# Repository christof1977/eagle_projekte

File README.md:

# eagle_projekte
Eagle Projekte

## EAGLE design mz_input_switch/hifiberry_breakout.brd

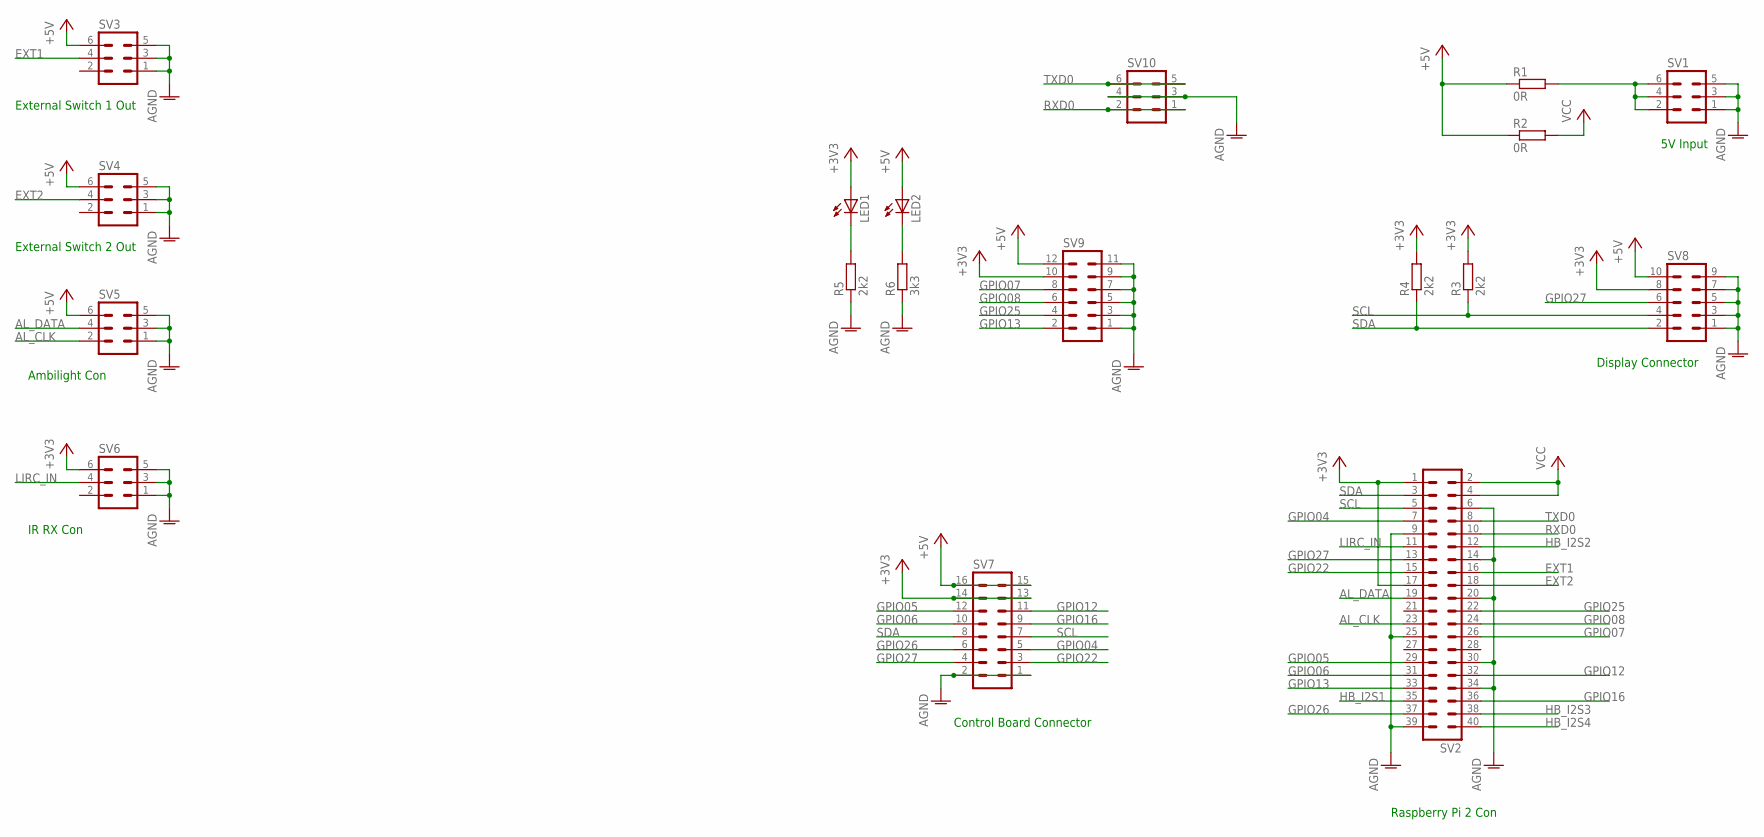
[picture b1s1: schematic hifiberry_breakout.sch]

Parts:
LED1, LED2: LEDCHIPLED_0603; CHIPLED_0603
R1, R2: 0R; R1206
R3, R4, R5: 2k2; R0603
R6: 3k3; R0603
SV1, SV3, SV4, SV5, SV6, SV10: MA03-2
SV2: MA20-2
SV7: MA08-2
SV8: MA05-2
SV9: MA06-2

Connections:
+3V3: LED1.A, R3.2, R4.2, SV2.1, SV2.17, SV6.6, SV7.13, SV7.14, SV8.8, SV9.10
+5V: LED2.A, R1.1, R2.1, SV3.6, SV4.6, SV5.6, SV7.15, SV7.16, SV8.10, SV9.12
AGND: R5.1, R6.1, SV1.1, SV1.3, SV1.5, SV2.6, SV2.9, SV2.14, SV2.20, SV2.25, SV2.30, SV2.34, SV2.39, SV3.1, SV3.3, SV3.5, SV4.1, SV4.3, SV4.5, SV5.1, SV5.3, SV5.5, SV6.1, SV6.3, SV6.5, SV7.1, SV7.2, SV8.1, SV8.3, SV8.5, SV8.7, SV8.9, SV9.1, SV9.3, SV9.5, SV9.7, SV9.9, SV9.11, SV10.3, SV10.4
AL_CLK: SV2.23, SV5.2
AL_DATA: SV2.19, SV5.4
EXT1: SV2.16, SV3.4
EXT2: SV2.18, SV4.4
GPIO04: SV2.7, SV7.5
GPIO05: SV2.29, SV7.12
GPIO06: SV2.31, SV7.10
GPIO07: SV2.26, SV9.8
GPIO08: SV2.24, SV9.6
GPIO12: SV2.32, SV7.11
GPIO13: SV2.33, SV9.2
GPIO16: SV2.36, SV7.9
GPIO22: SV2.15, SV7.3
GPIO25: SV2.22, SV9.4
GPIO26: SV2.37, SV7.6
GPIO27: SV2.13, SV7.4, SV8.6
HB_I2S1: SV2.35
HB_I2S2: SV2.12
HB_I2S3: SV2.38
HB_I2S4: SV2.40
LIRC_IN: SV2.11, SV6.4
unnamed: LED2.C, R6.2
unnamed: R1.2, SV1.2, SV1.4, SV1.6
unnamed: LED1.C, R5.2
RXD0: SV2.10, SV10.1, SV10.2
SCL: R3.1, SV2.5, SV7.7, SV8.4
SDA: R4.1, SV2.3, SV7.8, SV8.2
TXD0: SV2.8, SV10.5, SV10.6
VCC: R2.2, SV2.2, SV2.4

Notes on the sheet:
5V Input
External Switch 1 Out
External Switch 2 Out
Ambilight Con
IR RX Con
Raspberry Pi 2 Con
Control Board Connector
Display Connector

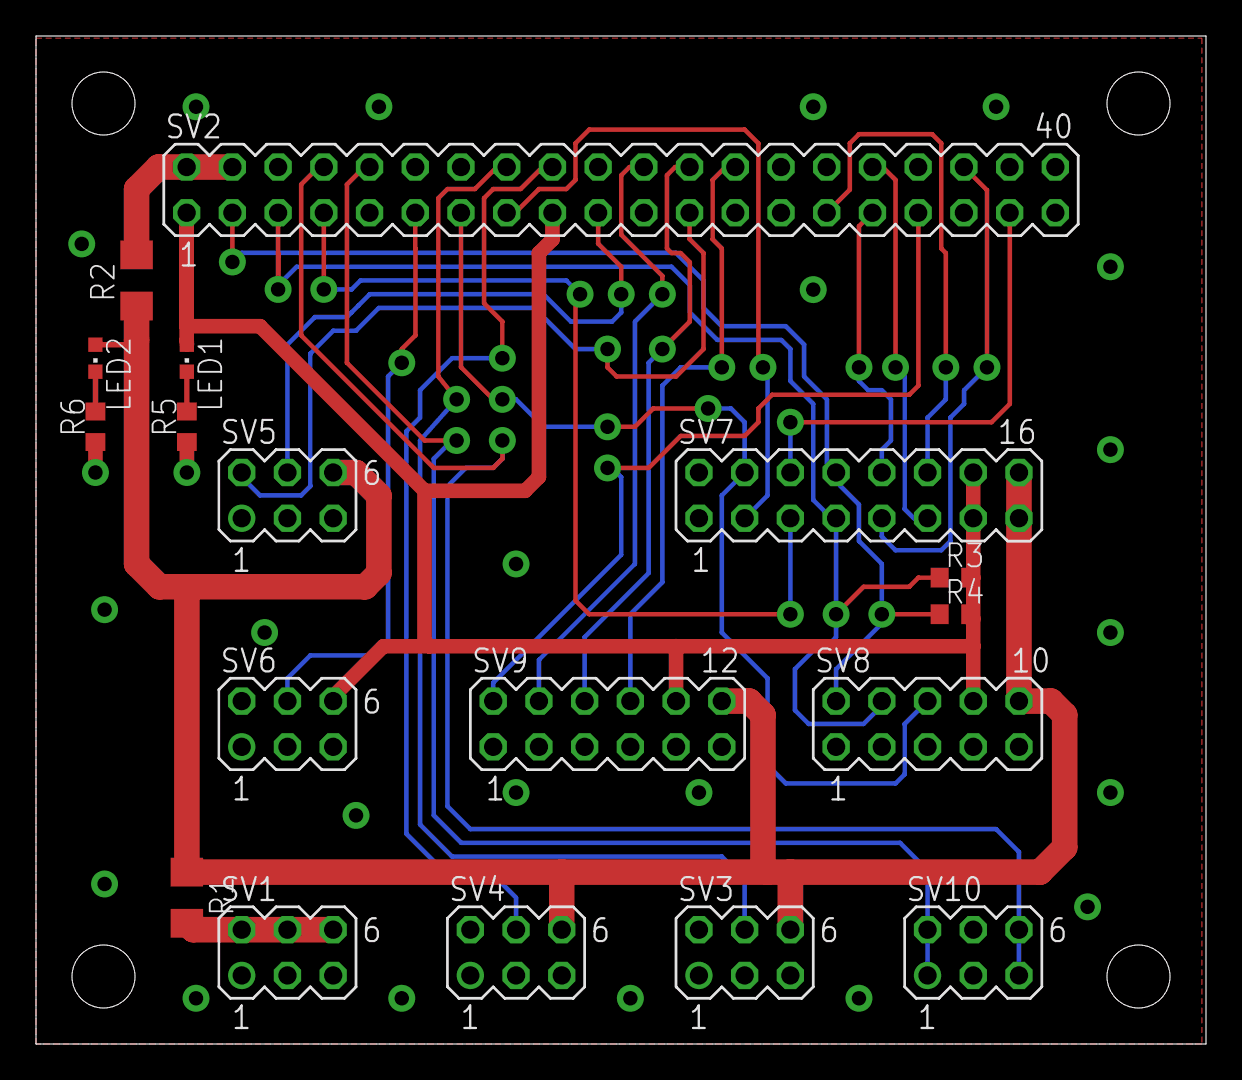
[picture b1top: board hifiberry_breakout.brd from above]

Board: 2 copper layers, 65.0 x 56.0 mm, 18 parts (0 on the bottom side), 28 nets.

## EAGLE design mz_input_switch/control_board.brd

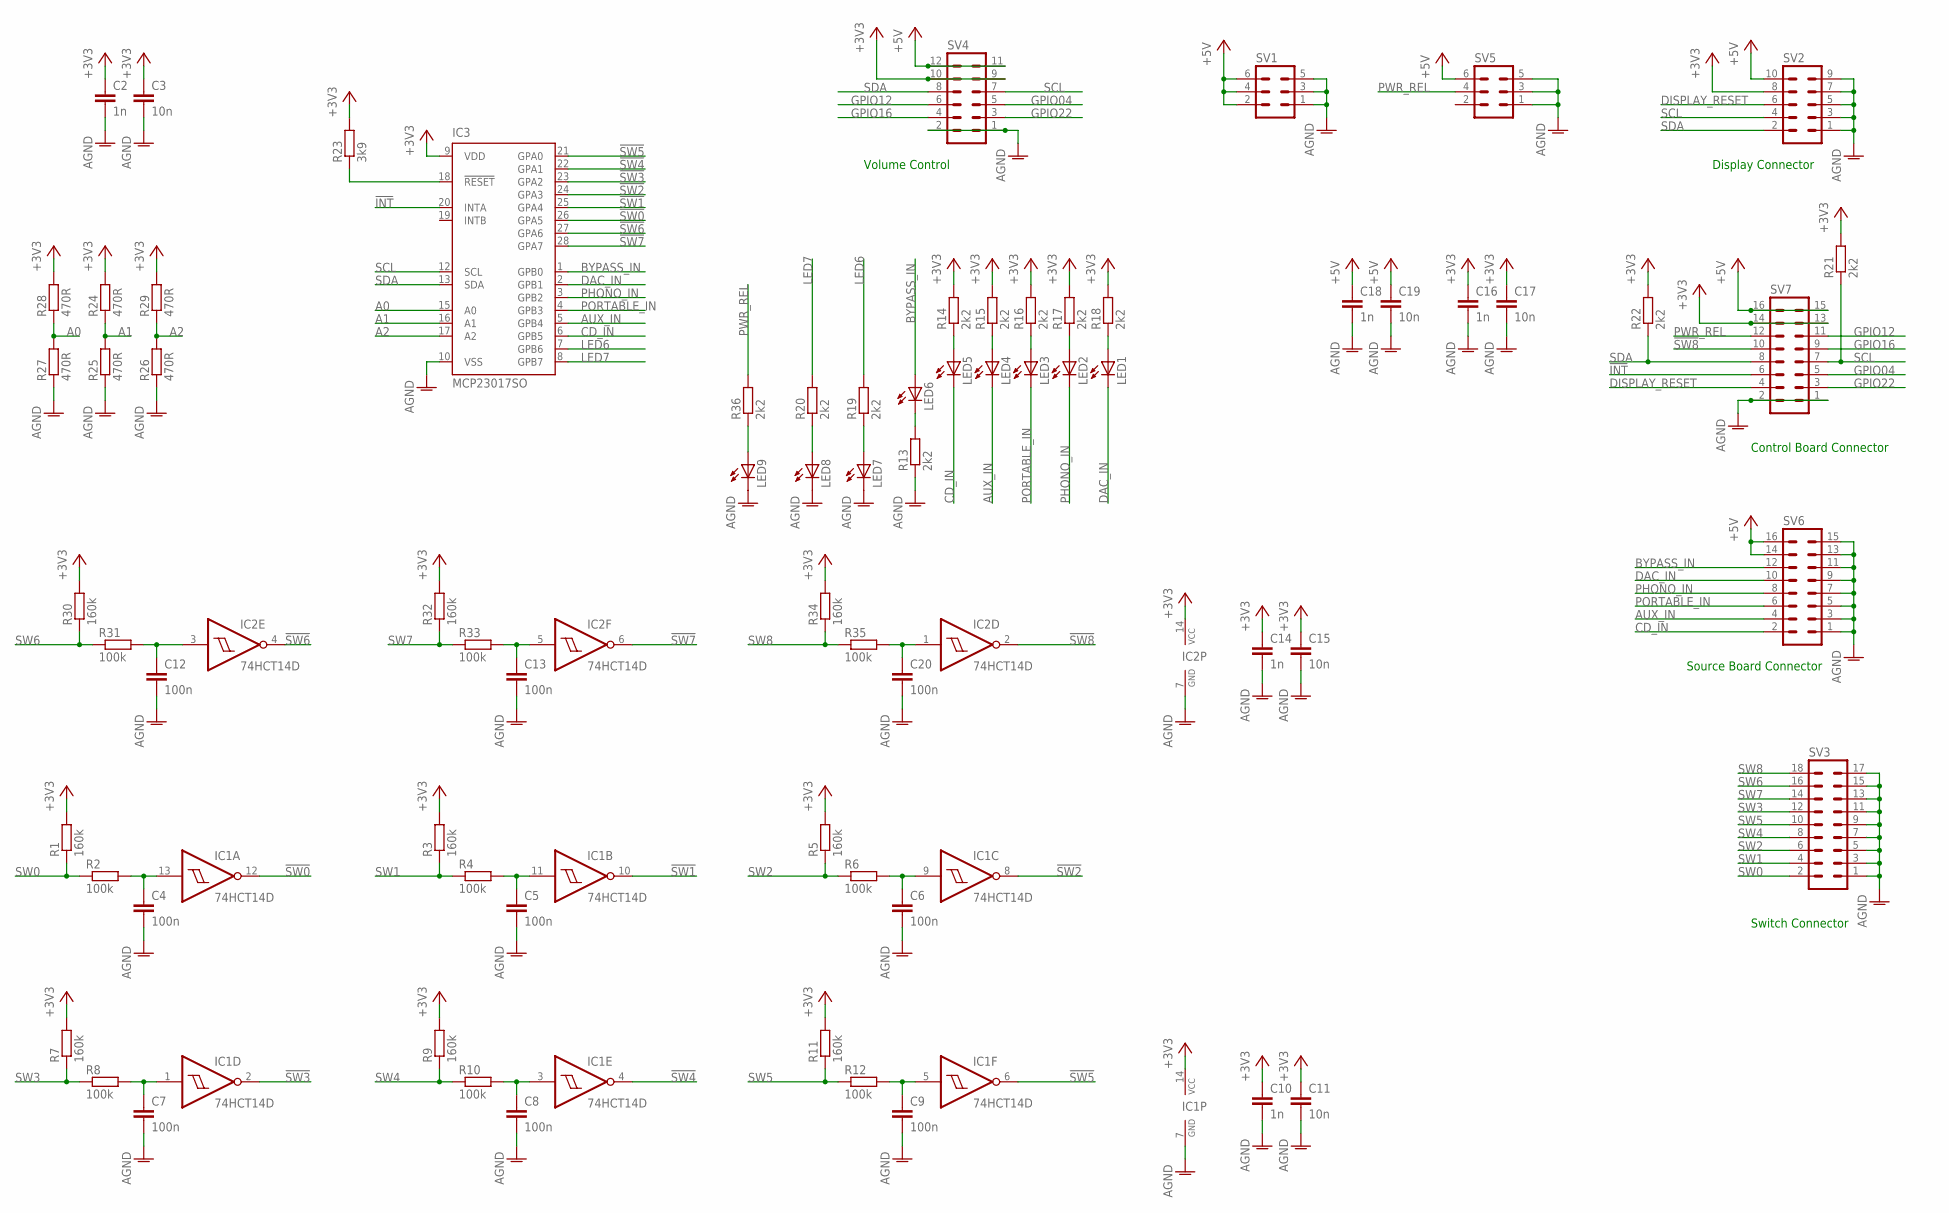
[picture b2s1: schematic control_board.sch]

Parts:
C2, C10, C14, C16, C18: 1n; C0603
C3, C11, C15, C17, C19: 10n; C0603
C4, C5, C6, C7, C8, C9, C12, C13, C20: 100n; C0603
IC1, IC2: 74HCT14D; SO14
IC3: MCP23017SO; SO28W
LED1, LED2, LED3, LED4, LED5, LED6, LED7, LED8, LED9: LEDCHIPLED_0603; CHIPLED_0603
R1, R3, R5, R7, R9, R11, R30, R32, R34: 160k; R0603
R2, R4, R6, R8, R10, R12, R31, R33, R35: 100k; R0603
R13, R14, R15, R16, R17, R18, R19, R20, R21, R22, R36: 2k2; R0603
R23: 3k9; R0603
R24, R25, R26, R27, R28, R29: 470R; R0603
SV1, SV5: MA03-2
SV2: MA05-2
SV3: MA09-2
SV4: MA06-2
SV6, SV7: MA08-2

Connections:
!INT: IC3.20 (INTA), SV7.6
!SW0: IC1.12 (O), IC3.26 (GPA5)
!SW1: IC1.10 (O), IC3.25 (GPA4)
!SW2: IC1.8 (O), IC3.24 (GPA3)
!SW3: IC1.2 (O), IC3.23 (GPA2)
!SW4: IC1.4 (O), IC3.22 (GPA1)
!SW5: IC1.6 (O), IC3.21 (GPA0)
!SW6: IC2.4 (O), IC3.27 (GPA6)
!SW7: IC2.6 (O), IC3.28 (GPA7)
!SW8: IC2.2 (O), SV7.10
+3V3: C2.1, C3.1, C10.1, C11.1, C14.1, C15.1, C16.1, C17.1, IC1.14 (VCC), IC2.14 (VCC), IC3.9 (VDD), R1.2, R3.2, R5.2, R7.2, R9.2, R11.2, R14.2, R15.2, R16.2, R17.2, R18.2, R21.2, R22.2, R23.2, R24.2, R28.2, R29.2, R30.2, R32.2, R34.2, SV2.8, SV4.9, SV4.10, SV7.13, SV7.14
+5V: C18.1, C19.1, SV1.2, SV1.4, SV1.6, SV2.10, SV4.11, SV4.12, SV5.6, SV6.14, SV6.16, SV7.15, SV7.16
A0: IC3.15 (A0), R27.2, R28.1
A1: IC3.16 (A1), R24.1, R25.2
A2: IC3.17 (A2), R26.2, R29.1
AGND: C2.2, C3.2, C4.2, C5.2, C6.2, C7.2, C8.2, C9.2, C10.2, C11.2, C12.2, C13.2, C14.2, C15.2, C16.2, C17.2, C18.2, C19.2, C20.2, IC1.7 (GND), IC2.7 (GND), IC3.10 (VSS), LED7.C, LED8.C, LED9.C, R13.1, R25.1, R26.1, R27.1, SV1.1, SV1.3, SV1.5, SV2.1, SV2.3, SV2.5, SV2.7, SV2.9, SV3.1, SV3.3, SV3.5, SV3.7, SV3.9, SV3.11, SV3.13, SV3.15, SV3.17, SV4.1, SV4.2, SV5.1, SV5.3, SV5.5, SV6.1, SV6.3, SV6.5, SV6.7, SV6.9, SV6.11, SV6.13, SV6.15, SV7.1, SV7.2
AUX_IN: IC3.5 (GPB4), LED4.C, SV6.4
BYPASS_IN: IC3.1 (GPB0), LED6.A, SV6.12
CD_IN: IC3.6 (GPB5), LED5.C, SV6.2
DAC_IN: IC3.2 (GPB1), LED1.C, SV6.10
DISPLAY_RESET: SV2.6, SV7.4
GPIO04: SV4.5, SV7.5
GPIO12: SV4.6, SV7.11
GPIO16: SV4.4, SV7.9
GPIO22: SV4.3, SV7.3
LED6: IC3.7 (GPB6), R19.2
LED7: IC3.8 (GPB7), R20.2
unnamed: C20.1, IC2.1 (I), R35.2
unnamed: LED5.A, R14.1
unnamed: LED4.A, R15.1
unnamed: LED3.A, R16.1
unnamed: LED2.A, R17.1
unnamed: LED1.A, R18.1
unnamed: LED7.A, R19.1
unnamed: LED8.A, R20.1
unnamed: LED6.C, R13.2
unnamed: LED9.A, R36.1
unnamed: C12.1, IC2.3 (I), R31.2
unnamed: C4.1, IC1.13 (I), R2.2
unnamed: C13.1, IC2.5 (I), R33.2
unnamed: C5.1, IC1.11 (I), R4.2
unnamed: IC3.18 (!RESET), R23.1
unnamed: C6.1, IC1.9 (I), R6.2
unnamed: C7.1, IC1.1 (I), R8.2
unnamed: C8.1, IC1.3 (I), R10.2
unnamed: C9.1, IC1.5 (I), R12.2
PHONO_IN: IC3.3 (GPB2), LED2.C, SV6.8
PORTABLE_IN: IC3.4 (GPB3), LED3.C, SV6.6
PWR_REL: R36.2, SV5.4, SV7.12
SCL: IC3.12 (SCL), R21.1, SV2.4, SV4.7, SV7.7
SDA: IC3.13 (SDA), R22.1, SV2.2, SV4.8, SV7.8
SW0: R1.1, R2.1, SV3.2
SW1: R3.1, R4.1, SV3.4
SW2: R5.1, R6.1, SV3.6
SW3: R7.1, R8.1, SV3.12
SW4: R9.1, R10.1, SV3.8
SW5: R11.1, R12.1, SV3.10
SW6: R30.1, R31.1, SV3.16
SW7: R32.1, R33.1, SV3.14
SW8: R34.1, R35.1, SV3.18

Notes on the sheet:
Display Connector
Source Board Connector
Control Board Connector
Switch Connector
Volume Control

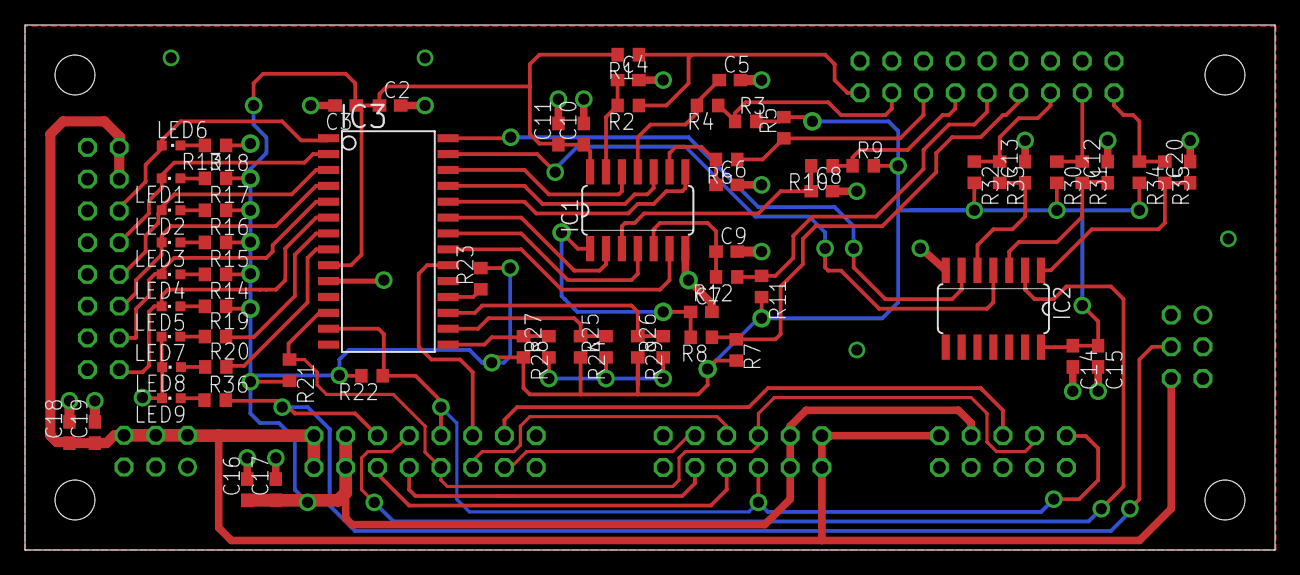
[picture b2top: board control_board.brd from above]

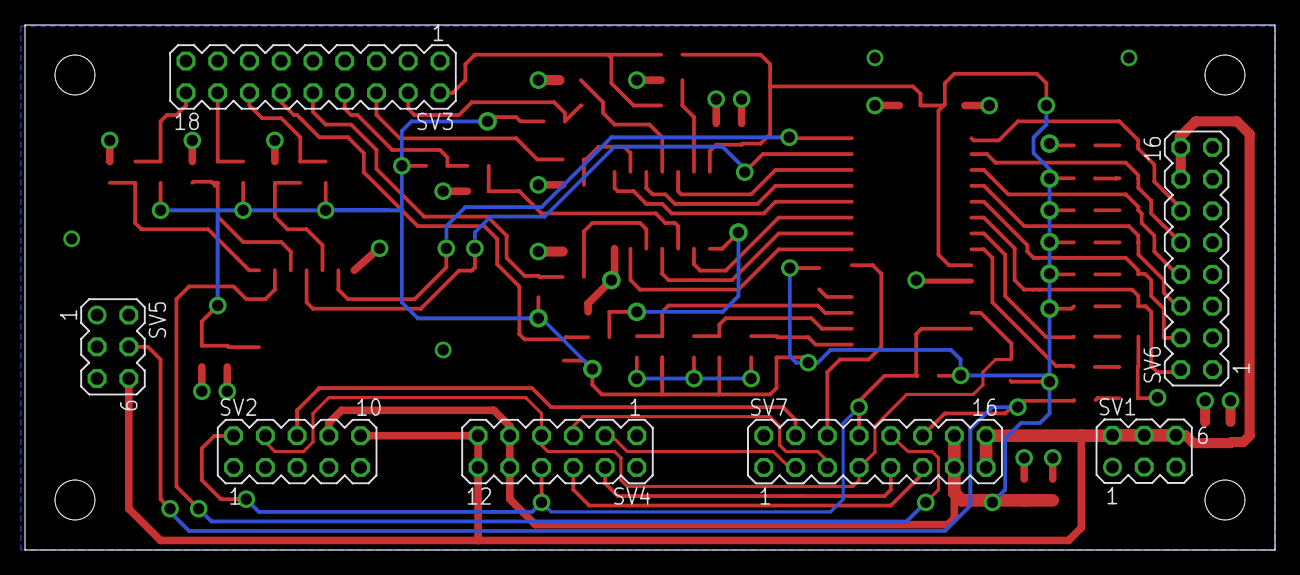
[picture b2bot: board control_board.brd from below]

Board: 2 copper layers, 100.0 x 42.0 mm, 74 parts (7 on the bottom side), 60 nets.

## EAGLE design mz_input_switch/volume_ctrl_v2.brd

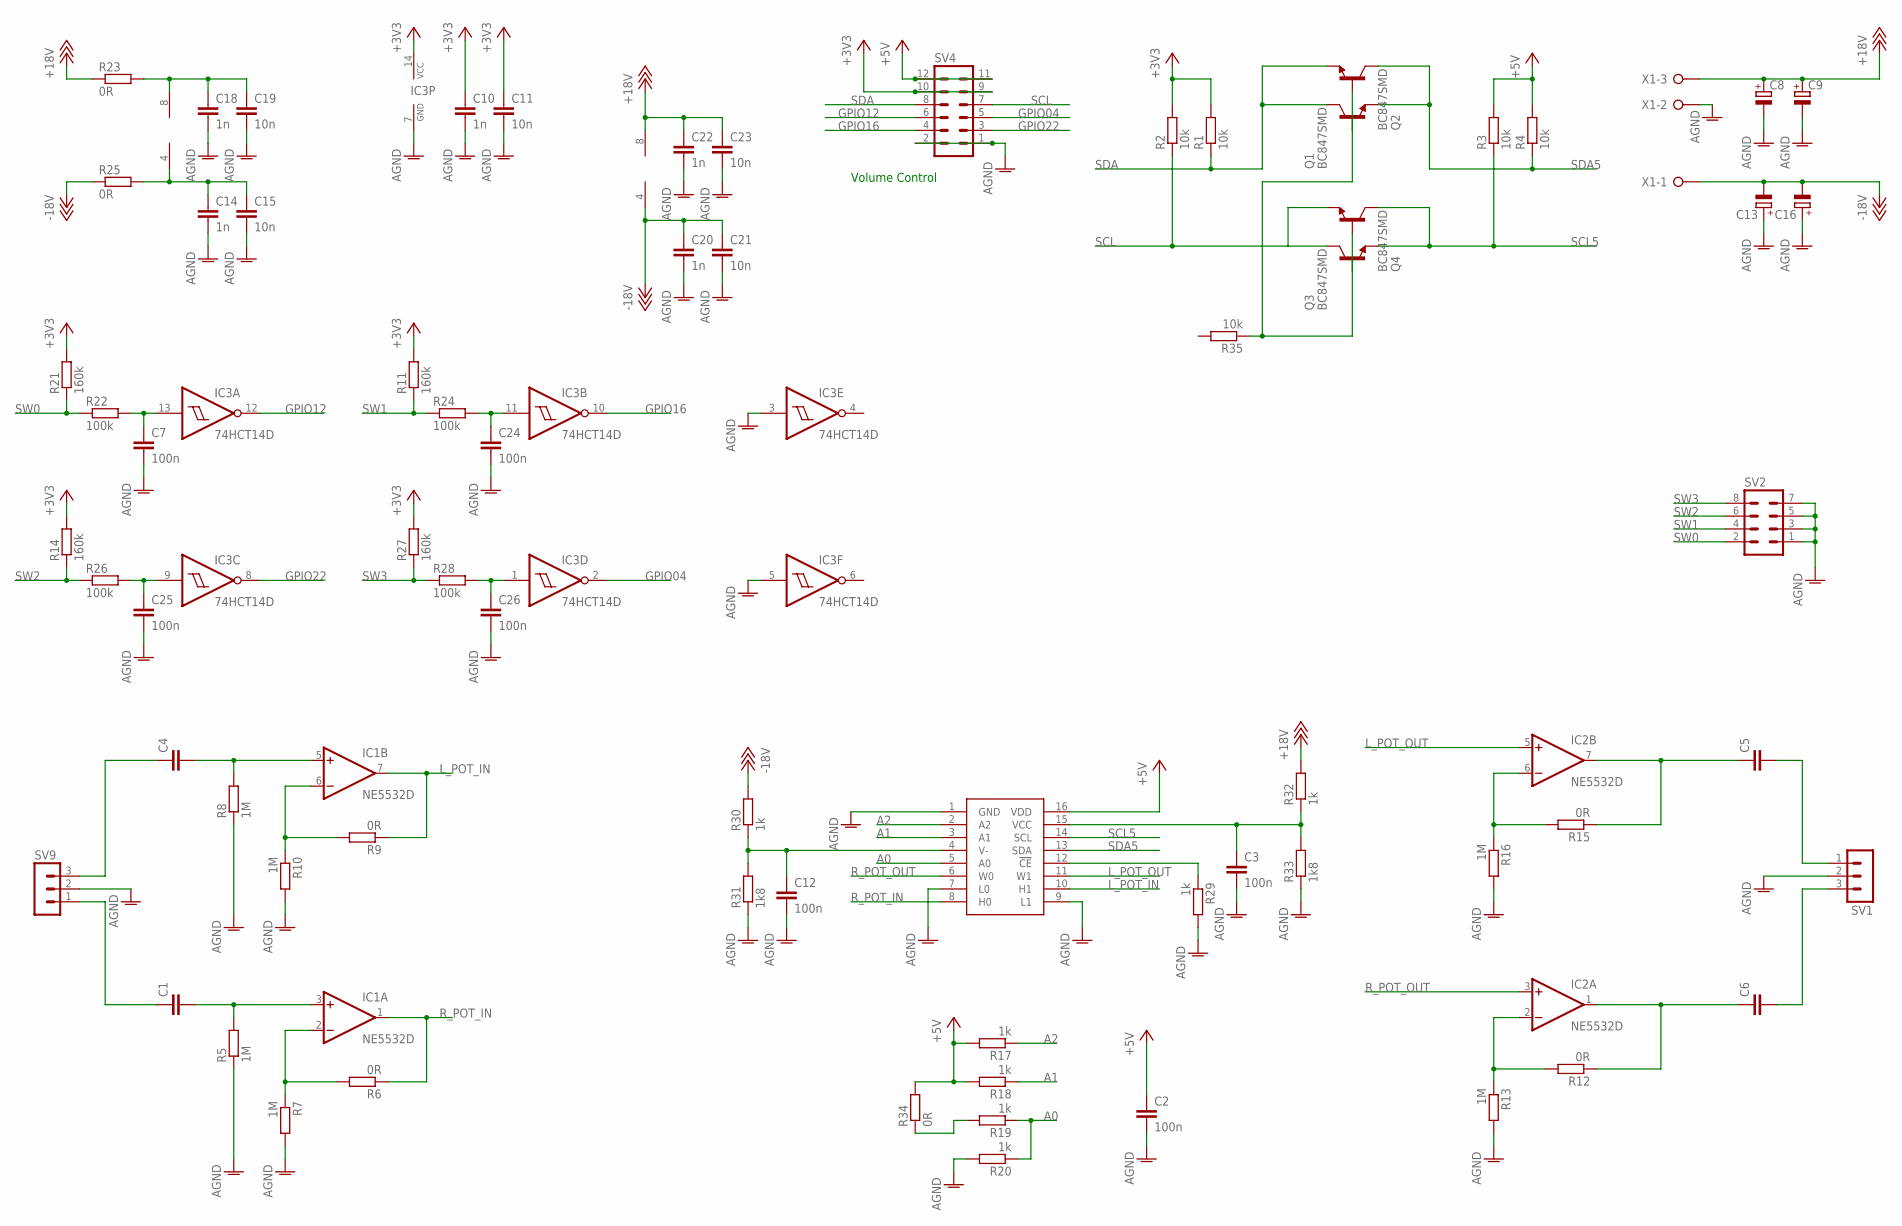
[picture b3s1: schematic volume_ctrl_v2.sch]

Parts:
C1, C4, C5, C6: C22/7; C22.5B7
C2, C3, C7, C12, C24, C25, C26: 100n; C0603
C8, C9, C13, C16: CPOL-EUE5-10.5; E5-10,5
C10, C14, C18, C20, C22: 1n; C0603
C11, C15, C19, C21, C23: 10n; C0603
IC1, IC2: NE5532D; SO08
IC3: 74HCT14D; SO14
IC4: DS1882; SO16
Q1, Q2, Q3, Q4: BC847SMD; SOT23
R1, R2, R3, R35: 10k; R0805
R4: 10k; R1206
R5, R7, R8, R10, R13, R16: 1M; R0805
R6, R9, R12, R15: 0R; R0805
R11, R14: 160k; R1206
R17, R18, R19, R20, R29, R30, R32: 1k; R0805
R21, R27: 160k; R0603
R22, R24, R26, R28: 100k; R0603
R23, R25, R34: 0R; R1206
R31, R33: 1k8; R0805
SV1, SV9: MA03-1
SV2: MA04-2
SV4: MA06-2
X1: W237-3E

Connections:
+3V3: C10.1, C11.1, IC3.14 (VCC), R1.2, R2.2, R11.2, R14.2, R21.2, R27.2, SV4.9, SV4.10
+5V: C2.1, IC4.16 (VDD), R3.2, R4.2, R17.2, R18.2, R34.2, SV4.11, SV4.12
+18V: C8.+, C9.+, C22.1, C23.1, IC2.8 (V+), R23.1, R32.2, X1.3
-18V: C13.-, C16.-, C20.1, C21.1, IC2.4 (V-), R25.1, R30.2, X1.1
A0: IC4.5 (A0), R19.1, R20.1
A1: IC4.3 (A1), R18.1
A2: IC4.2 (A2), R17.1
AGND: C2.2, C3.2, C7.2, C8.-, C9.-, C10.2, C11.2, C12.2, C13.+, C14.2, C15.2, C16.+, C18.2, C19.2, C20.2, C21.2, C22.2, C23.2, C24.2, C25.2, C26.2, IC3.3 (I), IC3.5 (I), IC3.7 (GND), IC4.1 (GND), IC4.7 (L0), IC4.9 (L1), R5.1, R7.2, R8.1, R10.2, R13.2, R16.2, R20.2, R29.2, R31.1, R33.1, SV1.2, SV2.1, SV2.3, SV2.5, SV2.7, SV4.1, SV4.2, SV9.2, X1.2
GPIO04: IC3.2 (O), SV4.5
GPIO12: IC3.12 (O), SV4.6
GPIO16: IC3.10 (O), SV4.4
GPIO22: IC3.8 (O), SV4.3
L_POT_IN: IC1.7 (OUT), IC4.10 (H1), R9.1
L_POT_OUT: IC2.5 (+IN), IC4.11 (W1)
unnamed: IC1.2 (-IN), R6.2, R7.1
unnamed: C1.2, IC1.3 (+IN), R5.2
unnamed: C4.1, SV9.3
unnamed: IC1.6 (-IN), R9.2, R10.1
unnamed: C4.2, IC1.5 (+IN), R8.2
unnamed: C1.1, SV9.1
unnamed: IC2.2 (-IN), R12.2, R13.1
unnamed: C5.2, SV1.1
unnamed: IC2.6 (-IN), R15.2, R16.1
unnamed: C6.2, SV1.3
unnamed: C5.1, IC2.7 (OUT), R15.1
unnamed: C6.1, IC2.1 (OUT), R12.1
unnamed: C7.1, IC3.13 (I), R22.2
unnamed: C24.1, IC3.11 (I), R24.2
unnamed: C25.1, IC3.9 (I), R26.2
unnamed: C26.1, IC3.1 (I), R28.2
unnamed: IC4.12 (!CE), R29.1
unnamed: C12.1, IC4.4 (V-), R30.1, R31.2
unnamed: C3.1, IC4.15 (VCC), R32.1, R33.2
unnamed: C18.1, C19.1, IC1.8 (V+), R23.2
unnamed: C14.1, C15.1, IC1.4 (V-), R25.2
unnamed: R19.2, R34.1
unnamed: Q1.1 (B), Q2.1 (B), Q3.1 (B), Q4.1 (B), R35.1
R_POT_IN: IC1.1 (OUT), IC4.8 (H0), R6.1
R_POT_OUT: IC2.3 (+IN), IC4.6 (W0)
SCL: Q3.3 (C), Q4.2 (E), R2.1, SV4.7
SCL5: IC4.14 (SCL), Q3.2 (E), Q4.3 (C), R3.1
SDA: Q1.3 (C), Q2.2 (E), R1.1, SV4.8
SDA5: IC4.13 (SDA), Q1.2 (E), Q2.3 (C), R4.1
SW0: R21.1, R22.1, SV2.2
SW1: R11.1, R24.1, SV2.4
SW2: R14.1, R26.1, SV2.6
SW3: R27.1, R28.1, SV2.8

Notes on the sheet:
Volume Control

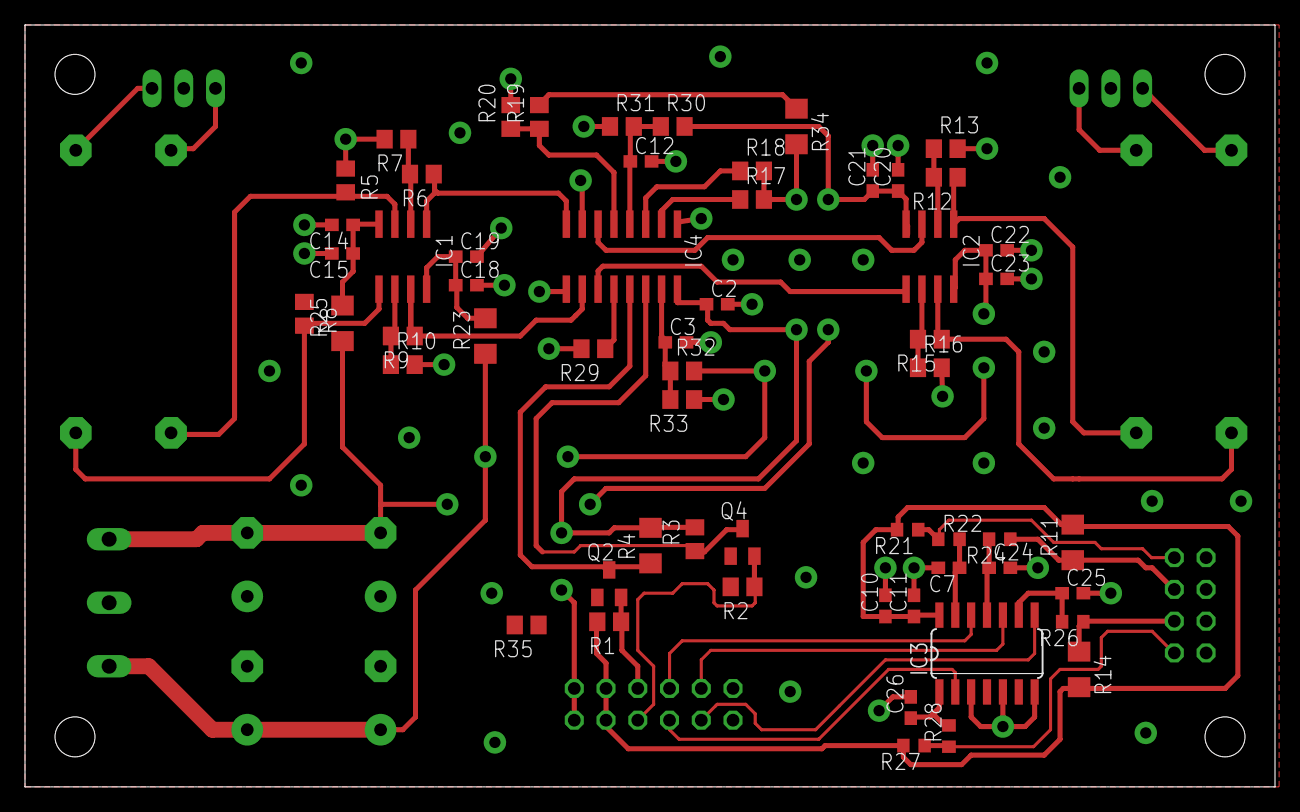
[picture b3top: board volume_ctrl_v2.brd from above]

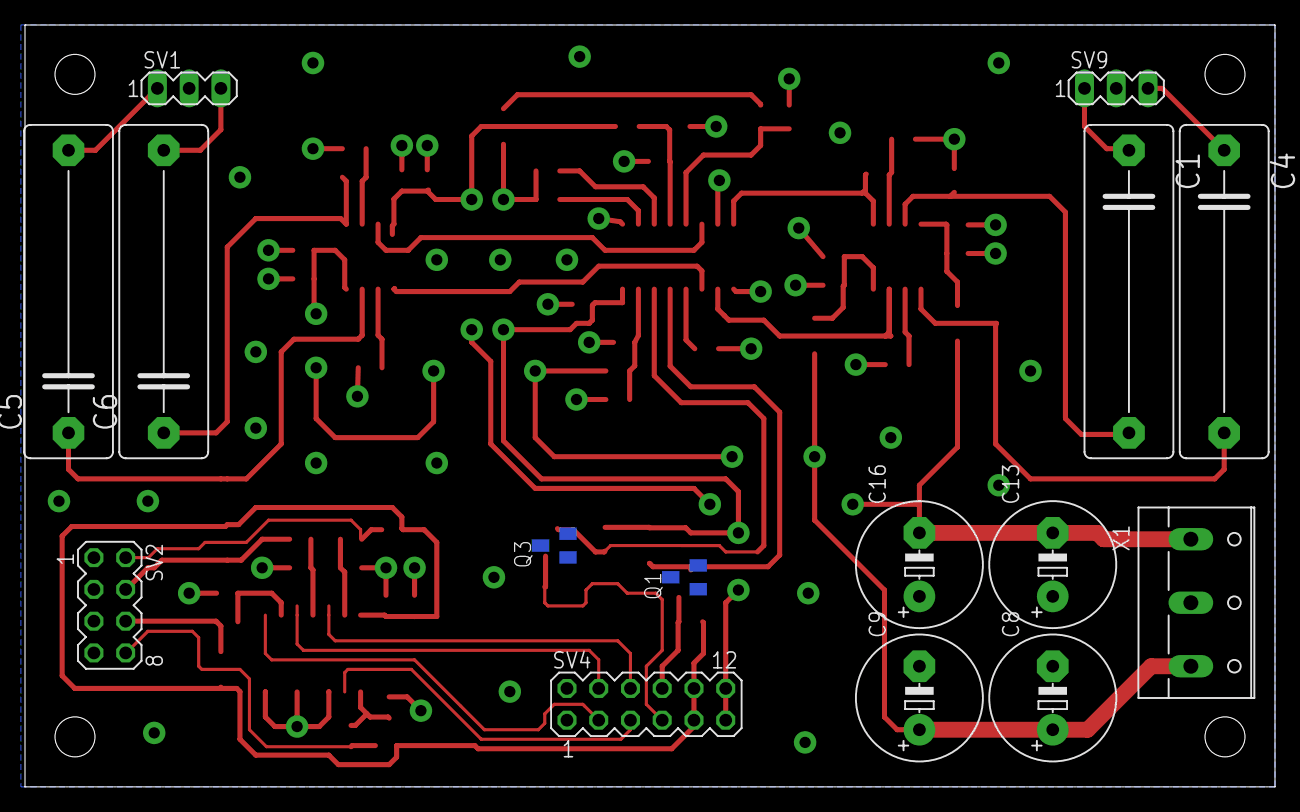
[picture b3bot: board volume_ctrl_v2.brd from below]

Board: 2 copper layers, 100.0 x 61.0 mm, 73 parts (15 on the bottom side), 47 nets.

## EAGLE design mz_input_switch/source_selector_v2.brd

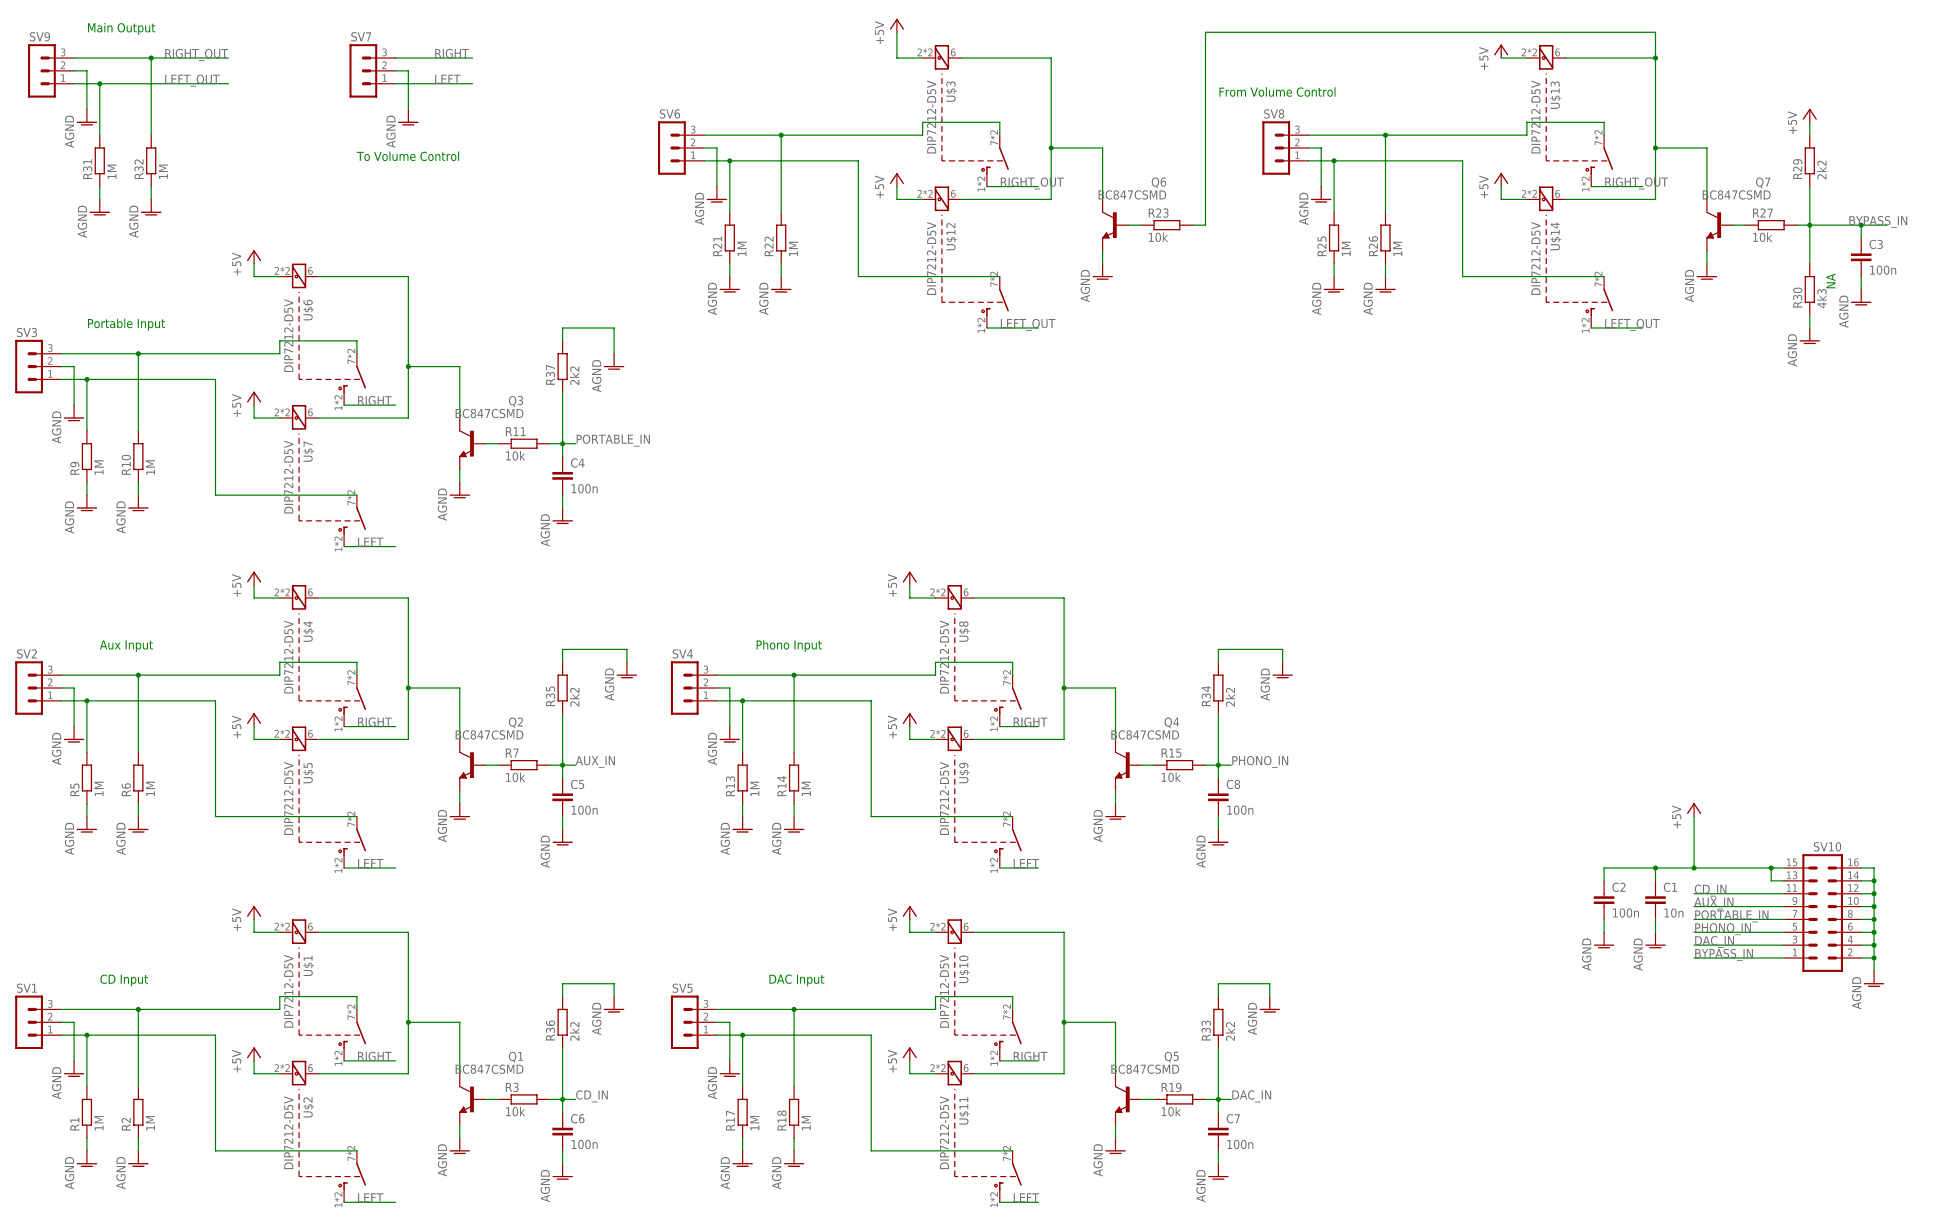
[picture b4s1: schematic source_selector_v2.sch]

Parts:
C1: 10n; C0603
C2, C3, C4, C5, C6, C7, C8: 100n; C0603
Q1, Q2, Q3, Q4, Q5, Q6, Q7: BC847CSMD; SOT23
R1, R2, R5, R6, R9, R10, R13, R14, R17, R18, R21, R22, R25, R26, R31, R32: 1M; R0603
R3, R7, R11, R15, R19, R23, R27: 10k; R0603
R29, R33, R34, R35, R36, R37: 2k2; R0603
R30: 4k3; R0603
SV1, SV2, SV3, SV4, SV5, SV6, SV7, SV8, SV9: MA03-1
SV10: MA08-2
U$1, U$2, U$3, U$4, U$5, U$6, U$7, U$8, U$9, U$10, U$11, U$12, U$13, U$14: DIP7212-D5V; DP-07

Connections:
+5V: C1.1, C2.1, R29.2, SV10.13, SV10.15, U$1.2 (1), U$1.13 (1), U$2.2 (1), U$2.13 (1), U$3.2 (1), U$3.13 (1), U$4.2 (1), U$4.13 (1), U$5.2 (1), U$5.13 (1), U$6.2 (1), U$6.13 (1), U$7.2 (1), U$7.13 (1), U$8.2 (1), U$8.13 (1), U$9.2 (1), U$9.13 (1), U$10.2 (1), U$10.13 (1), U$11.2 (1), U$11.13 (1), U$12.2 (1), U$12.13 (1), U$13.2 (1), U$13.13 (1), U$14.2 (1), U$14.13 (1)
AGND: C1.2, C2.2, C3.2, C4.2, C5.2, C6.2, C7.2, C8.2, Q1.2 (E), Q2.2 (E), Q3.2 (E), Q4.2 (E), Q5.2 (E), Q6.2 (E), Q7.2 (E), R1.1, R2.1, R5.1, R6.1, R9.1, R10.1, R13.1, R14.1, R17.1, R18.1, R21.1, R22.1, R25.1, R26.1, R30.1, R31.1, R32.1, R33.2, R34.2, R35.2, R36.2, R37.2, SV1.2, SV2.2, SV3.2, SV4.2, SV5.2, SV6.2, SV7.2, SV8.2, SV9.2, SV10.2, SV10.4, SV10.6, SV10.8, SV10.10, SV10.12, SV10.14, SV10.16
AUX_IN: C5.1, R7.2, R35.1, SV10.9
BYPASS_IN: C3.1, R27.2, R29.1, R30.2, SV10.1
CD_IN: C6.1, R3.2, R36.1, SV10.11
DAC_IN: C7.1, R19.2, R33.1, SV10.3
LEFT: SV7.1, U$2.1 (6), U$2.14 (6), U$5.1 (6), U$5.14 (6), U$7.1 (6), U$7.14 (6), U$9.1 (6), U$9.14 (6), U$11.1 (6), U$11.14 (6)
LEFT_OUT: R31.2, SV9.1, U$12.1 (6), U$12.14 (6), U$14.1 (6), U$14.14 (6)
unnamed: R2.2, SV1.3, U$1.7 (5), U$1.8 (5)
unnamed: R1.2, SV1.1, U$2.7 (5), U$2.8 (5)
unnamed: Q1.1 (B), R3.1
unnamed: Q1.3 (C), U$1.6 (2), U$2.6 (2)
unnamed: R6.2, SV2.3, U$4.7 (5), U$4.8 (5)
unnamed: R5.2, SV2.1, U$5.7 (5), U$5.8 (5)
unnamed: Q2.1 (B), R7.1
unnamed: Q2.3 (C), U$4.6 (2), U$5.6 (2)
unnamed: R10.2, SV3.3, U$6.7 (5), U$6.8 (5)
unnamed: R9.2, SV3.1, U$7.7 (5), U$7.8 (5)
unnamed: Q3.1 (B), R11.1
unnamed: Q3.3 (C), U$6.6 (2), U$7.6 (2)
unnamed: R14.2, SV4.3, U$8.7 (5), U$8.8 (5)
unnamed: R13.2, SV4.1, U$9.7 (5), U$9.8 (5)
unnamed: Q4.1 (B), R15.1
unnamed: Q4.3 (C), U$8.6 (2), U$9.6 (2)
unnamed: R18.2, SV5.3, U$10.7 (5), U$10.8 (5)
unnamed: R17.2, SV5.1, U$11.7 (5), U$11.8 (5)
unnamed: Q5.1 (B), R19.1
unnamed: Q5.3 (C), U$10.6 (2), U$11.6 (2)
unnamed: R22.2, SV6.3, U$3.7 (5), U$3.8 (5)
unnamed: R21.2, SV6.1, U$12.7 (5), U$12.8 (5)
unnamed: Q6.1 (B), R23.1
unnamed: Q6.3 (C), U$3.6 (2), U$12.6 (2)
unnamed: R26.2, SV8.3, U$13.7 (5), U$13.8 (5)
unnamed: R25.2, SV8.1, U$14.7 (5), U$14.8 (5)
unnamed: Q7.1 (B), R27.1
unnamed: Q7.3 (C), R23.2, U$13.6 (2), U$14.6 (2)
PHONO_IN: C8.1, R15.2, R34.1, SV10.5
PORTABLE_IN: C4.1, R11.2, R37.1, SV10.7
RIGHT: SV7.3, U$1.1 (6), U$1.14 (6), U$4.1 (6), U$4.14 (6), U$6.1 (6), U$6.14 (6), U$8.1 (6), U$8.14 (6), U$10.1 (6), U$10.14 (6)
RIGHT_OUT: R32.2, SV9.3, U$3.1 (6), U$3.14 (6), U$13.1 (6), U$13.14 (6)

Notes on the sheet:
To Volume Control
From Volume Control
Main Output
Portable Input
Aux Input
CD Input
DAC Input
Phono Input

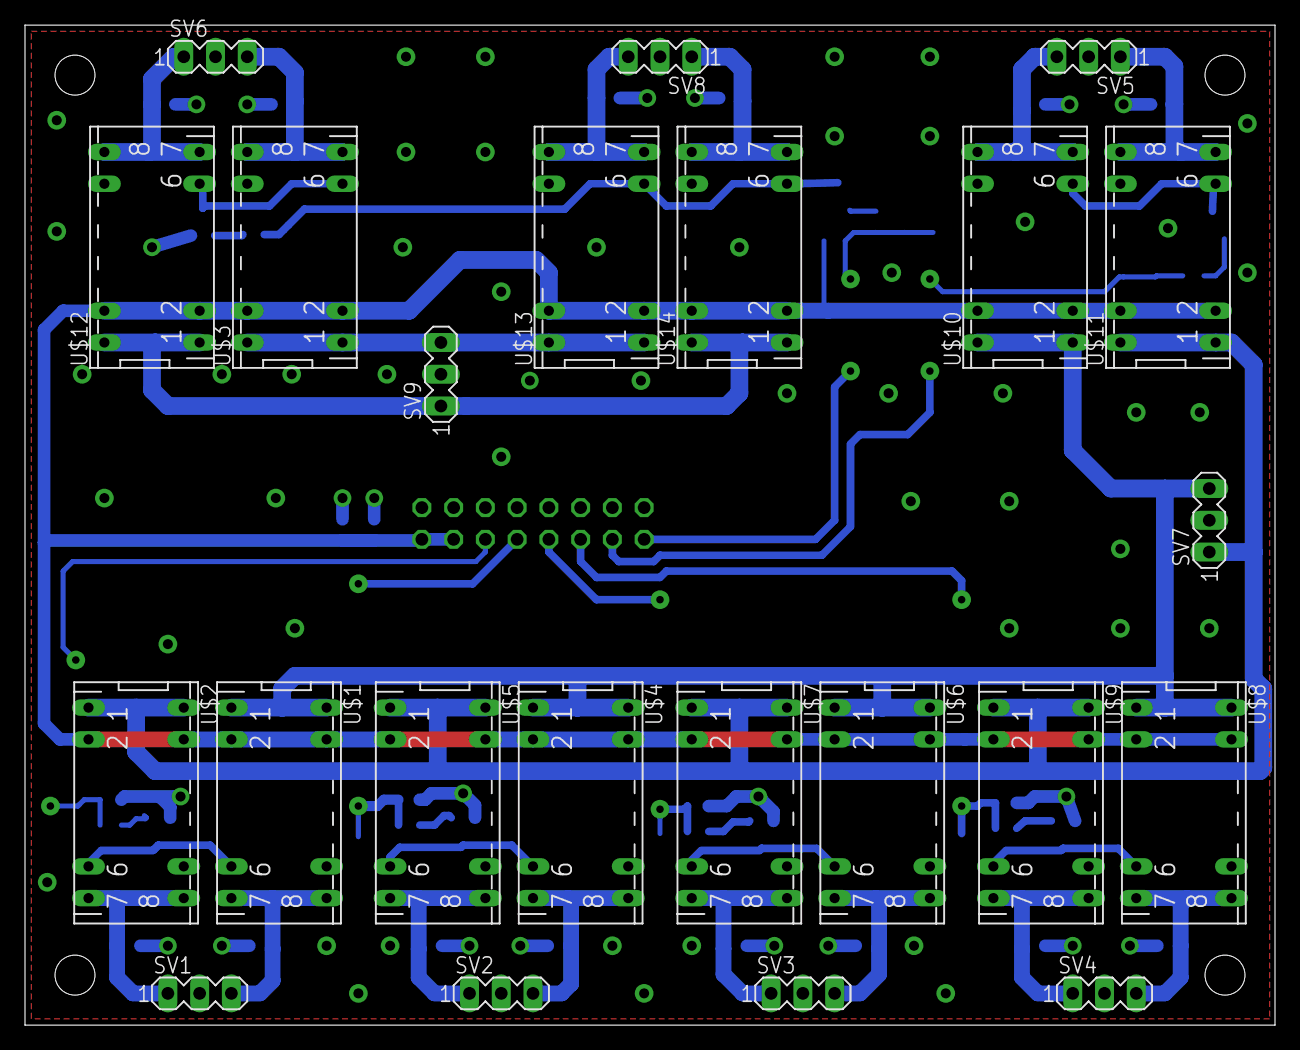
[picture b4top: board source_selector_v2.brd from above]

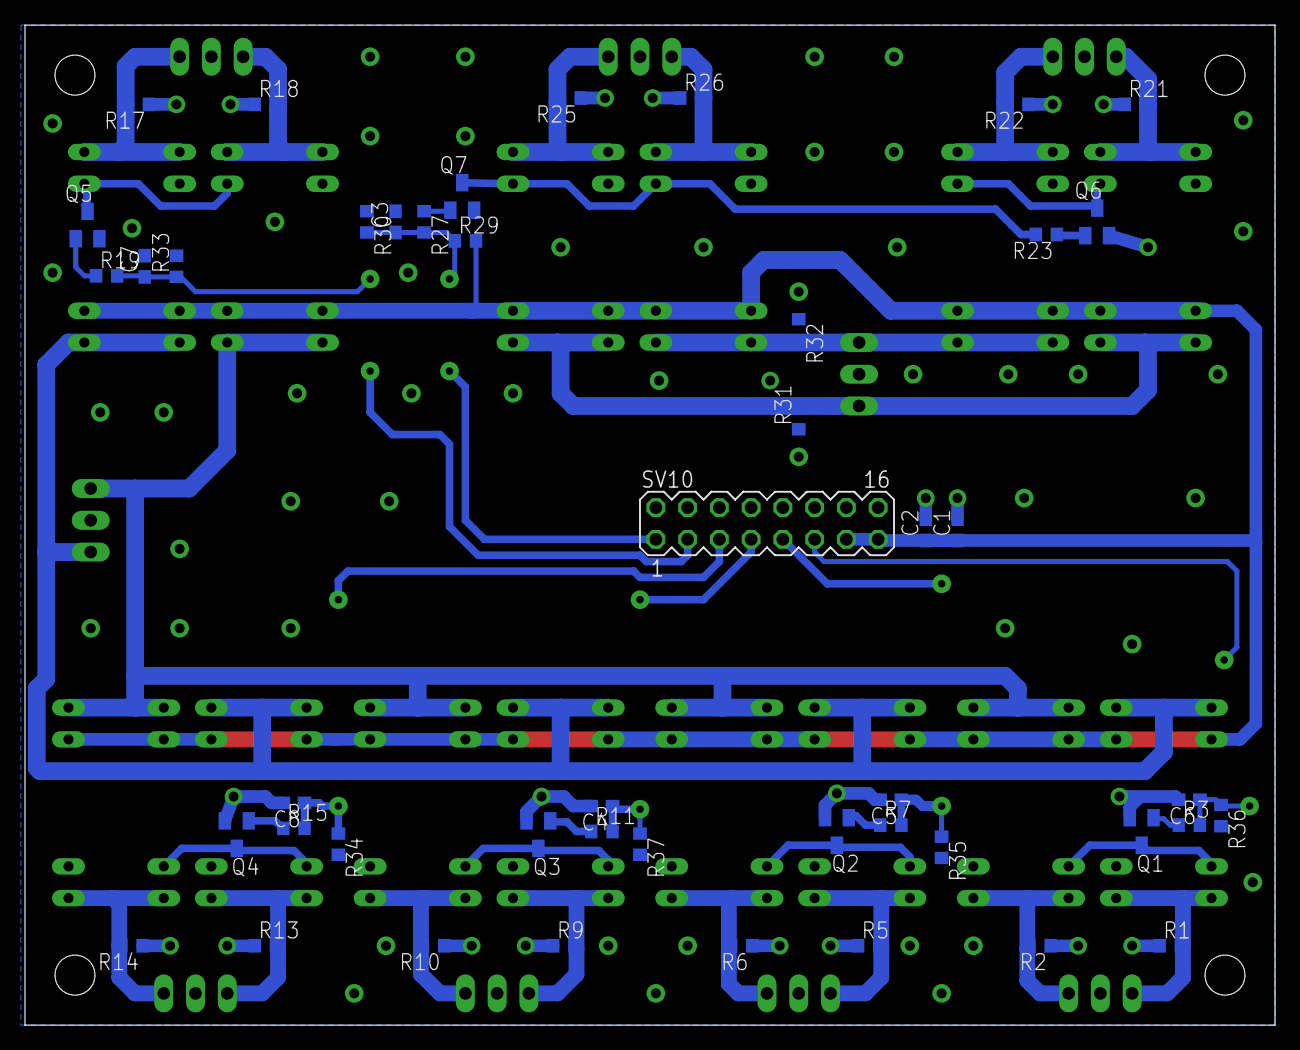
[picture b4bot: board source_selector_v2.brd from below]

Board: 2 copper layers, 100.0 x 80.0 mm, 69 parts (46 on the bottom side), 40 nets.
